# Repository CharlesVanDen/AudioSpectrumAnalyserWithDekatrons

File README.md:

# AudioSpectrumAnalyserWithDekatrons

I started this project with twenty 6802 dekatrons, not really knowing what the end result would be. That's why it was called TwentyDekatrons. 
Then I discovered the MSGEQ7 and it turned into an Stereo Audio Spectrum Analyzer with only seven Dekatrons. And now it's an article 
in Elektor issue september/ocotober 2022! For the extensive documentation, see: https://www.elektormagazine.nl/labs/i-finally-found-a-useful-application-for-dekatrons and https://www.elektor.com

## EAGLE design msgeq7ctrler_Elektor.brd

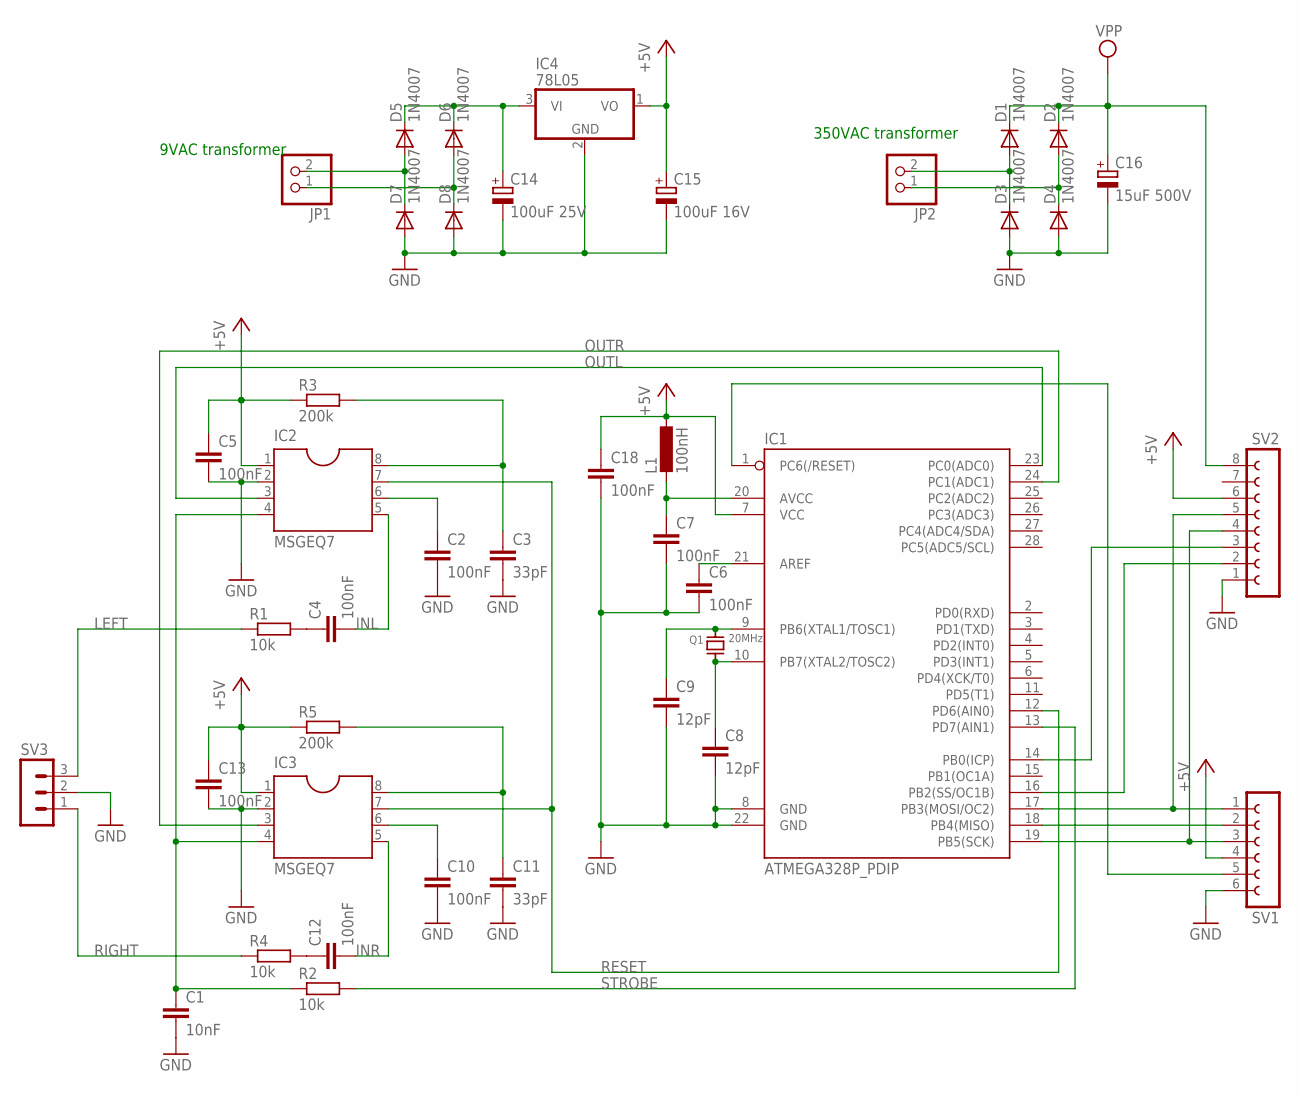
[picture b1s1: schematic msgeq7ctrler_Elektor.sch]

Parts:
C1: 10nF; C025-025X050
C2, C4, C5, C6, C7, C10, C12, C13, C18: 100nF; C025-025X050
C3, C11: 33pF; C025-025X050
C8, C9: 12pF; C025-025X050
C14: 100uF 25V; E2,5-6E
C15: 100uF 16V; E2,5-6E
C16: 15uF 500V; EB20D
D1, D2, D3, D4, D5, D6, D7, D8: 1N4007; DO41-10
IC1: ATMEGA328P_PDIP; DIL28-3
IC2, IC3: MSGEQ7; DIL08
IC4: 78L05; TO92SIL
JP1, JP2: PINHD-1X2; 1X02
L1: 100nH; 0207/10
Q1: 20MHz; XTAL
R1, R2, R4: 10k; 0207/12
R3, R5: 200k; 0207/12
SV1: FE06-1; FE06
SV2: FE08-1; FE08
SV3: MA03-1

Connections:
+5V: C5.1, C13.1, C15.+, C18.1, IC1.7 (VCC), IC2.1, IC3.1, IC4.1 (VO), L1.1, R3.1, R5.1, SV1.4, SV2.6
GND: C1.2, C2.2, C3.2, C5.2, C6.2, C7.2, C8.2, C9.2, C10.2, C11.2, C13.2, C14.-, C15.-, C16.-, C18.2, D3.A, D4.A, D7.A, D8.A, IC1.8 (GND), IC1.22 (GND), IC2.2, IC3.2, IC4.2 (GND), SV1.6, SV2.1, SV3.2
INL: C4.2, IC2.5
INR: C12.2, IC3.5
LEFT: R1.1, SV3.3
unnamed: C3.1, IC2.8, R3.2
unnamed: C4.1, R1.2
unnamed: C9.1, IC1.9 (PB6(XTAL1/TOSC1)), Q1.P$2
unnamed: C8.1, IC1.10 (PB7(XTAL2/TOSC2)), Q1.P$1
unnamed: C7.1, IC1.20 (AVCC), L1.2
unnamed: C6.1, IC1.21 (AREF)
unnamed: IC1.19 (PB5(SCK)), SV1.3, SV2.4
unnamed: IC1.18 (PB4(MISO)), SV1.2
unnamed: IC1.17 (PB3(MOSI/OC2)), SV1.1, SV2.5
unnamed: IC1.1 (PC6(/RESET)), SV1.5
unnamed: IC1.16 (PB2(SS/OC1B)), SV2.2
unnamed: IC1.14 (PB0(ICP)), SV2.3
unnamed: C11.1, IC3.8, R5.2
unnamed: C12.1, R4.2
unnamed: D1.A, D3.C, JP2.2
unnamed: D2.A, D4.C, JP2.1
unnamed: D5.A, D7.C, JP1.2
unnamed: D6.A, D8.C, JP1.1
OUTL: IC1.23 (PC0(ADC0)), IC2.3
OUTR: IC1.24 (PC1(ADC1)), IC3.3
RESET: IC1.12 (PD6(AIN0)), IC2.7, IC3.7
RIGHT: R4.1, SV3.1
STROBE: IC1.13 (PD7(AIN1)), R2.2
STROBE_RC: C1.1, IC2.4, IC3.4, R2.1
VGND: C2.1, IC2.6
VGND1: C10.1, IC3.6
VPP: C16.+, D1.C, D2.C, SV2.8
VPP1: C14.+, D5.C, D6.C, IC4.3 (VI)

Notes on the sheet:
350VAC transformer
9VAC transformer

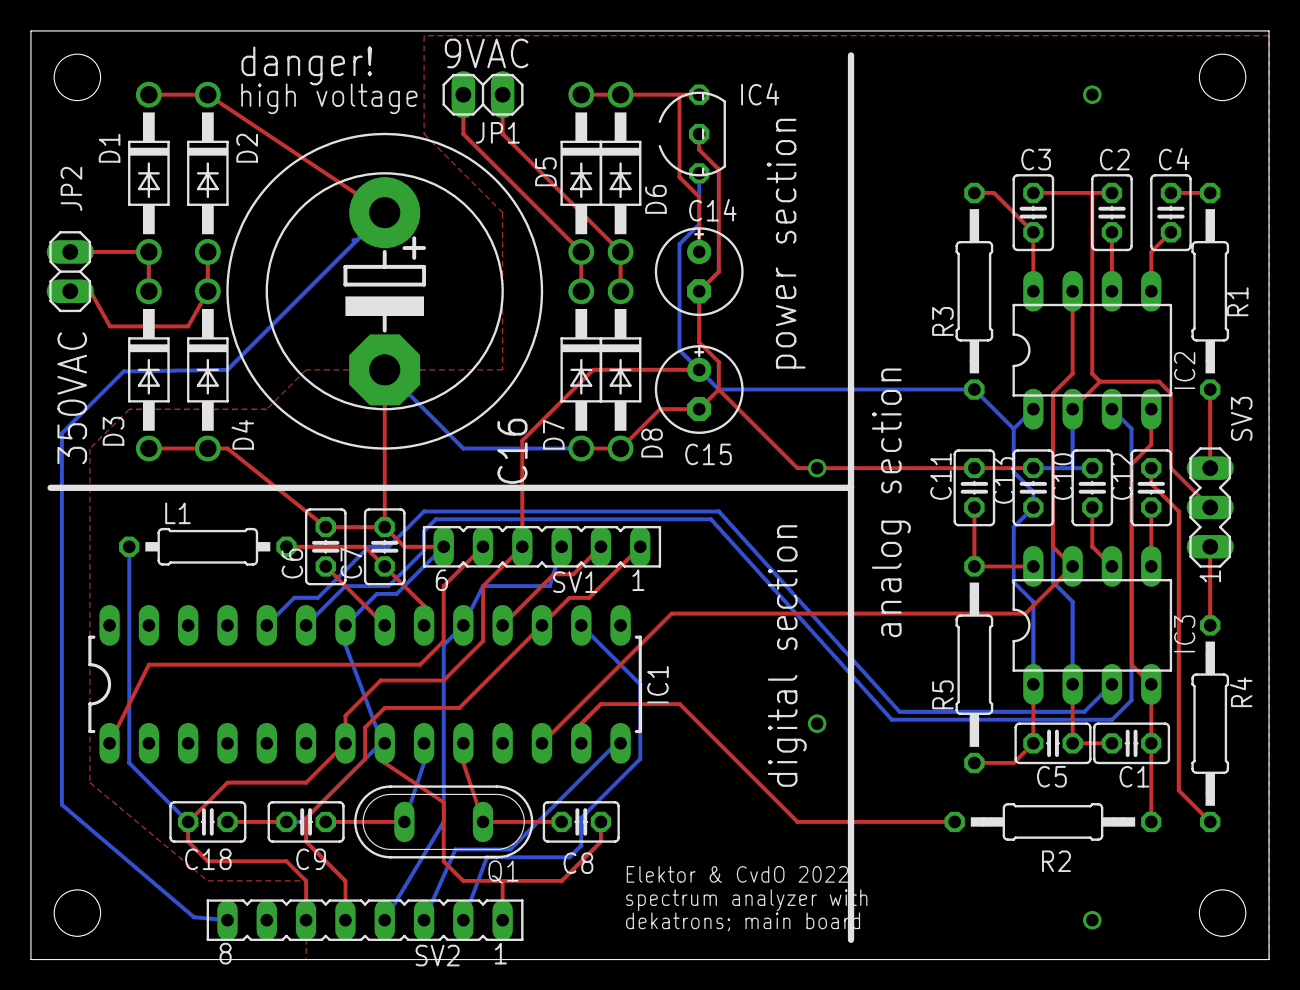
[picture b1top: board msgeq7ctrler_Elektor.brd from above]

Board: 2 copper layers, 80.0 x 60.0 mm, 41 parts (0 on the bottom side), 33 nets.

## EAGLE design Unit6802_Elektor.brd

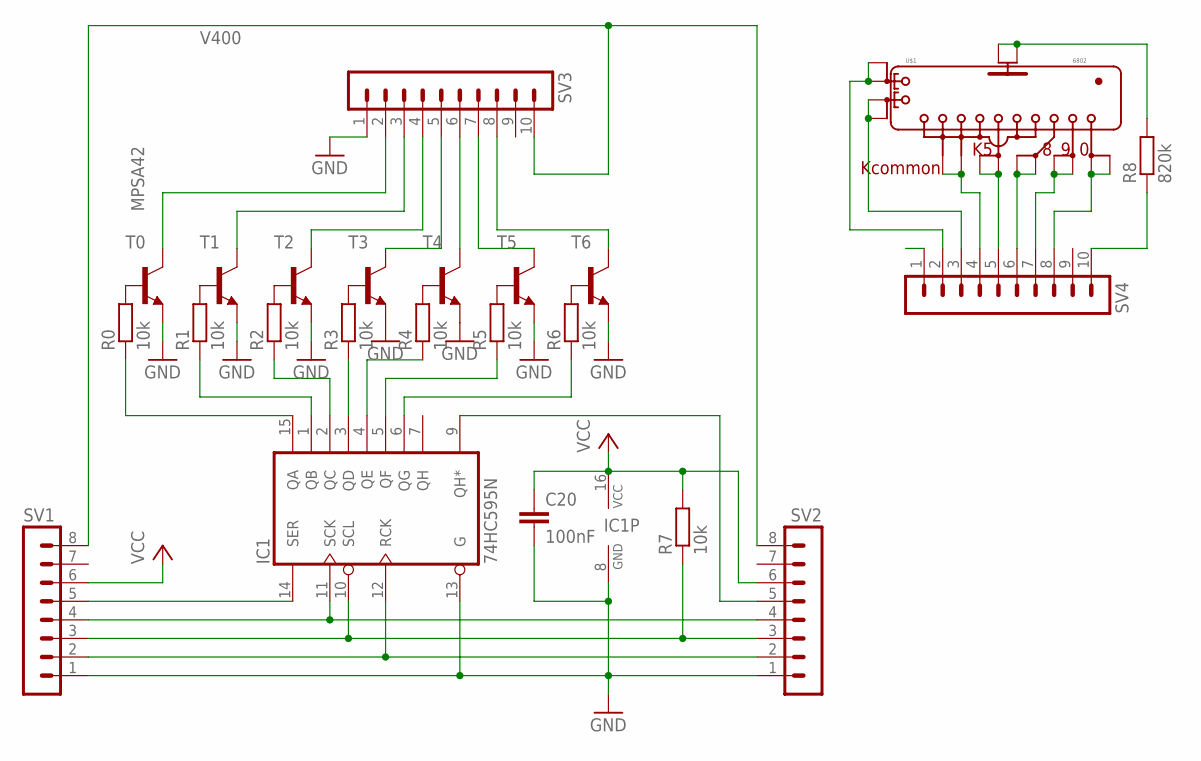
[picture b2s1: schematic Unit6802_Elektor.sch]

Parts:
C20: 100nF; C050-024X044
IC1: 74HC595N; DIL16
R0, R1, R2, R3, R4, R5, R6, R7: 10k; 0207/12
R8: 820k; 0207/12
SV1, SV2: MA08-1
SV3, SV4: MA10-1
T0: MPSA42; TO92-EBC
T1, T2, T3, T4, T5, T6: MPSA42-NPN-TO92-EBC; TO92-EBC
U$1: 6802; OCTAL2

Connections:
GND: C20.2, IC1.8 (GND), IC1.13 (G), SV1.1, SV2.1, SV3.1, T0.E, T1.E, T2.E, T3.E, T4.E, T5.E, T6.E
GND1: SV4.1
unnamed: SV3.4, T2.C
unnamed: SV3.5, T3.C
unnamed: SV3.8, T6.C
unnamed: SV3.7, T5.C
unnamed: SV3.6, T4.C
unnamed: SV3.2, T0.C
unnamed: SV3.3, T1.C
unnamed: SV4.4, U$1.1B (KCOMB), U$1.1C (KCOMA)
unnamed: IC1.15 (QA), R0.1
unnamed: IC1.1 (QB), R1.1
unnamed: IC1.2 (QC), R2.1
unnamed: IC1.3 (QD), R3.1
unnamed: IC1.4 (QE), R4.1
unnamed: IC1.5 (QF), R5.1
unnamed: IC1.6 (QG), R6.1
unnamed: R1.2, T1.B
unnamed: R2.2, T2.B
unnamed: R3.2, T3.B
unnamed: R4.2, T4.B
unnamed: R5.2, T5.B
unnamed: R6.2, T6.B
unnamed: R0.2, T0.B
unnamed: R8.1, SV4.10
unnamed: IC1.14 (SER), SV1.5
unnamed: IC1.11 (SCK), SV1.4, SV2.4
unnamed: IC1.9 (QH*), SV2.5
unnamed: IC1.10 (SCL), R7.1, SV1.3, SV2.3
unnamed: IC1.12 (RCK), SV1.2, SV2.2
unnamed: SV4.5, U$1.2B (K5B), U$1.2C (K5A)
unnamed: SV4.6, U$1.8B (K8B), U$1.8C (K8A)
unnamed: SV4.7, U$1.6B (K9B), U$1.6C (K9A)
unnamed: SV4.8, U$1.7B (K0B), U$1.7C (K0A)
unnamed: SV4.3, U$1.5B (G2B), U$1.5C (G2A)
unnamed: SV4.2, U$1.3B (G1B), U$1.3C (G1A)
unnamed: R8.2, U$1.4B (ANODEB), U$1.4C (ANODEA)
V400: SV1.8, SV2.8, SV3.10
VCC: C20.1, IC1.16 (VCC), R7.2, SV1.6, SV2.6

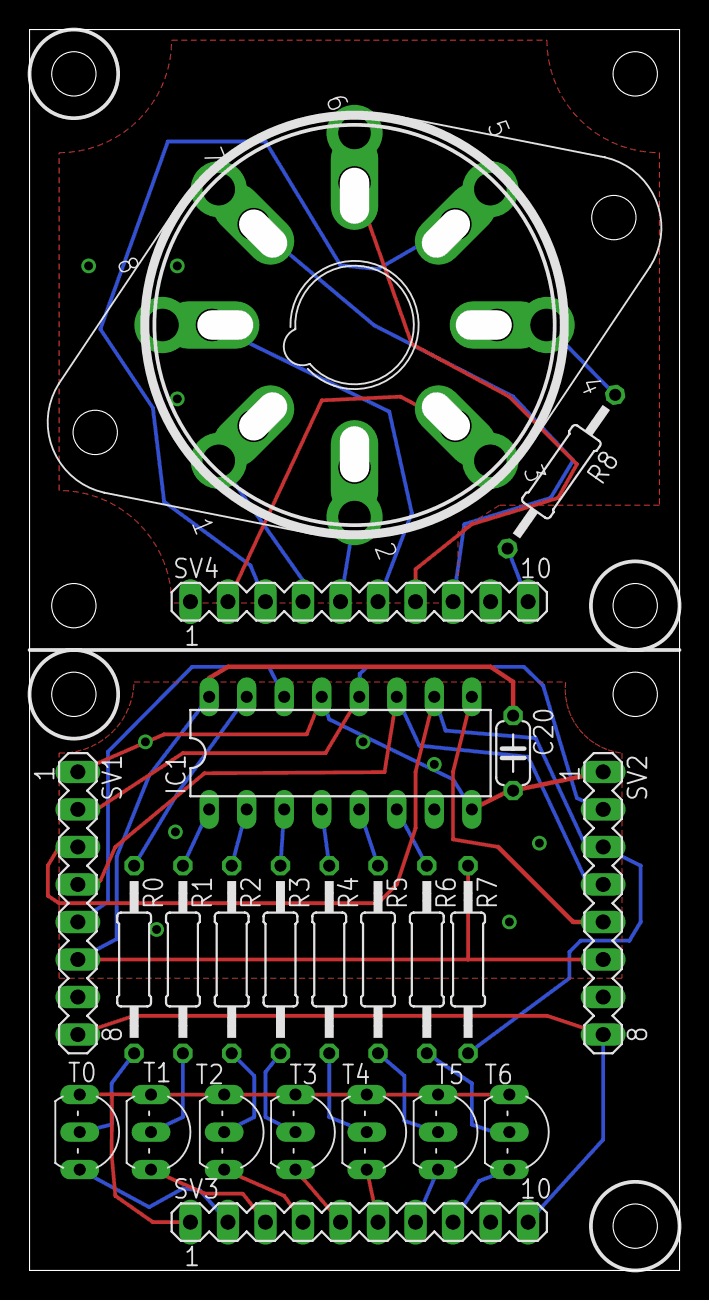
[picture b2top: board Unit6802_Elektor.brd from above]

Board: 2 copper layers, 44.0 x 84.0 mm, 23 parts (0 on the bottom side), 38 nets.

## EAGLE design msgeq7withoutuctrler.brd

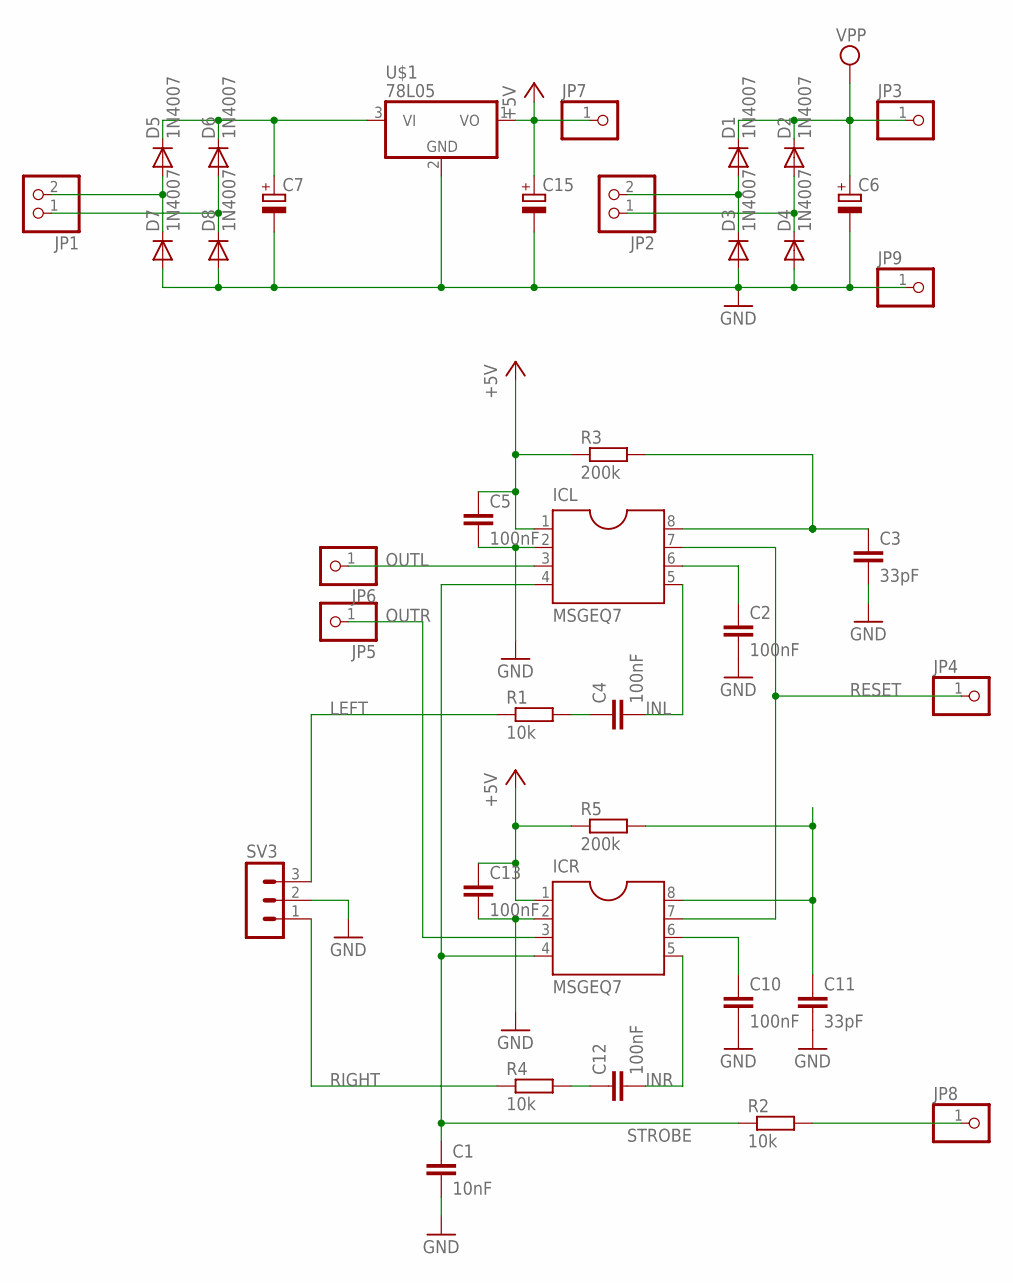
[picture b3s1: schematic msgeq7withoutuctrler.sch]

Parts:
C1: 10nF; C025-025X050
C2, C4, C5, C12, C13: 100nF; C025-025X050
C3, C11: 33pF; C025-025X050
C6: CPOL-EUE5-13; E5-13
C7, C15: CPOL-EUE2,5-6E; E2,5-6E
C10: 100nF; C050-024X044
D1, D2, D3, D4, D5, D6, D7, D8: 1N4007; DO41-10
ICL: MSGEQ7; DIL08
ICR: MSGEQ7; DIL08
JP1, JP2: PINHD-1X2; 1X02
JP3, JP4, JP5, JP6, JP7, JP8, JP9: PINHD-1X1CB; 1X01-CLEANBIG
R1, R2, R4: 10k; 0207/12
R3, R5: 200k; 0207/12
SV3: MA03-1
U$1: 78L05; TO92SIL

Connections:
+5V: C5.1, C13.1, C15.+, ICL.1, ICR.1, JP7.1, R3.1, R5.1, U$1.1 (VO)
GND: C1.2, C2.2, C3.2, C5.2, C6.-, C7.-, C10.2, C11.2, C13.2, C15.-, D3.A, D4.A, D7.A, D8.A, ICL.2, ICR.2, JP9.1, SV3.2, U$1.2 (GND)
INL: C4.2, ICL.5
INR: C12.2, ICR.5
LEFT: R1.1, SV3.3
unnamed: JP8.1, R2.2
unnamed: C3.1, ICL.8, R3.2
unnamed: C4.1, R1.2
unnamed: D5.A, D7.C, JP1.2
unnamed: D6.A, D8.C, JP1.1
unnamed: C11.1, ICR.8, R5.2
unnamed: C12.1, R4.2
unnamed: D1.A, D3.C, JP2.2
unnamed: D2.A, D4.C, JP2.1
OUTL: ICL.3, JP6.1
OUTR: ICR.3, JP5.1
RESET: ICL.7, ICR.7, JP4.1
RIGHT: R4.1, SV3.1
STROBE: C1.1, ICL.4, ICR.4, R2.1
VGND: C2.1, ICL.6
VGND1: C10.1, ICR.6
VPP: C6.+, D1.C, D2.C, JP3.1
VPP1: C7.+, D5.C, D6.C, U$1.3 (VI)

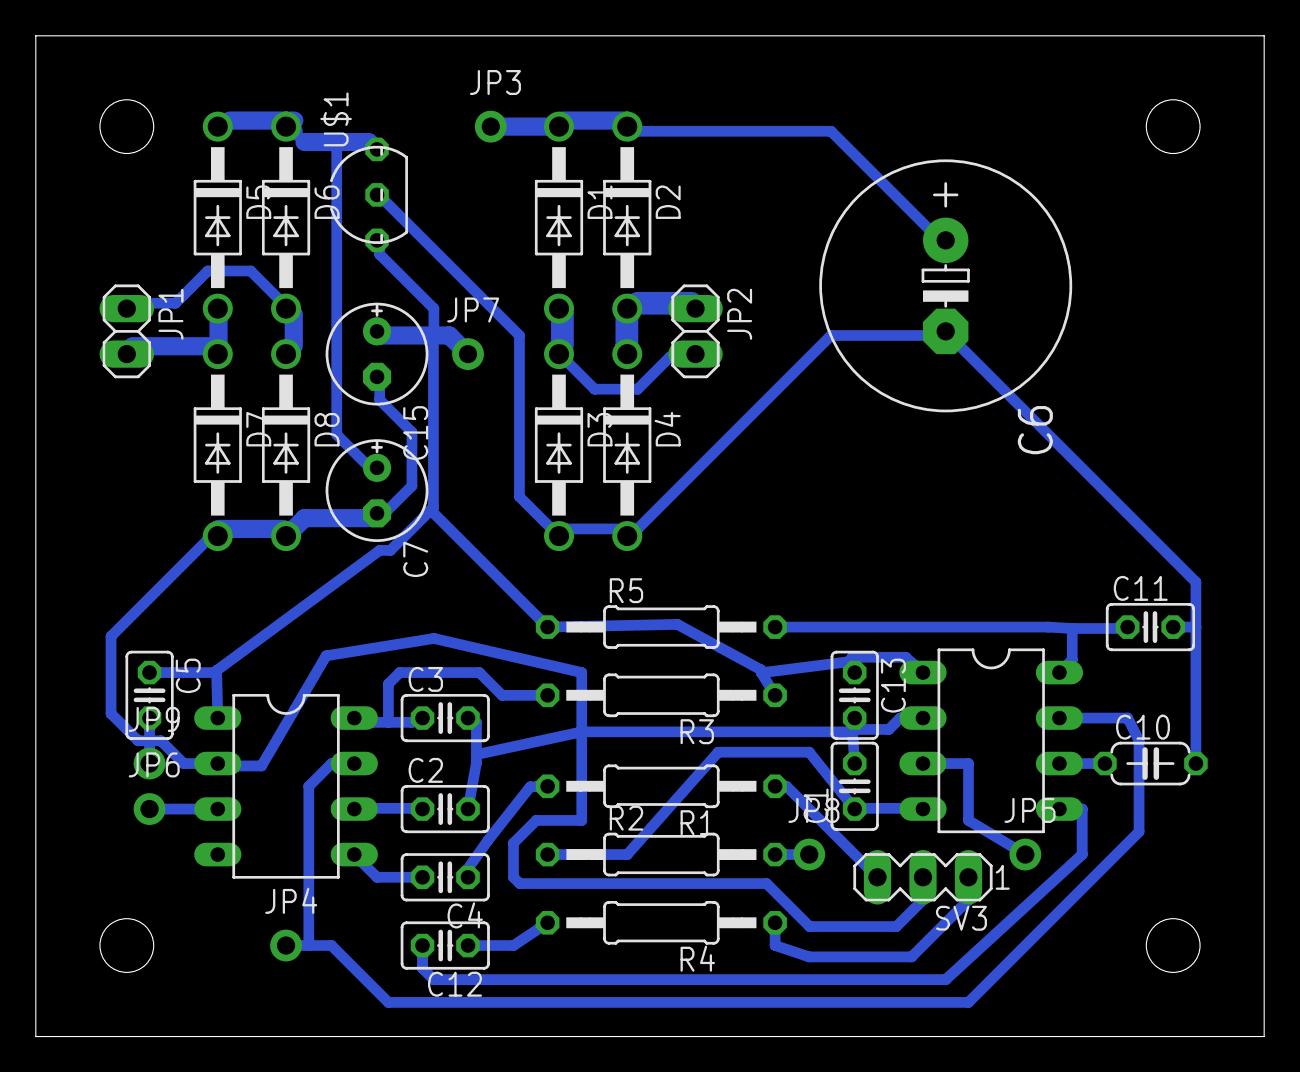
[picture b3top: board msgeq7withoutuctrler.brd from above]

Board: 2 copper layers, 68.6 x 55.9 mm, 38 parts (0 on the bottom side), 23 nets.

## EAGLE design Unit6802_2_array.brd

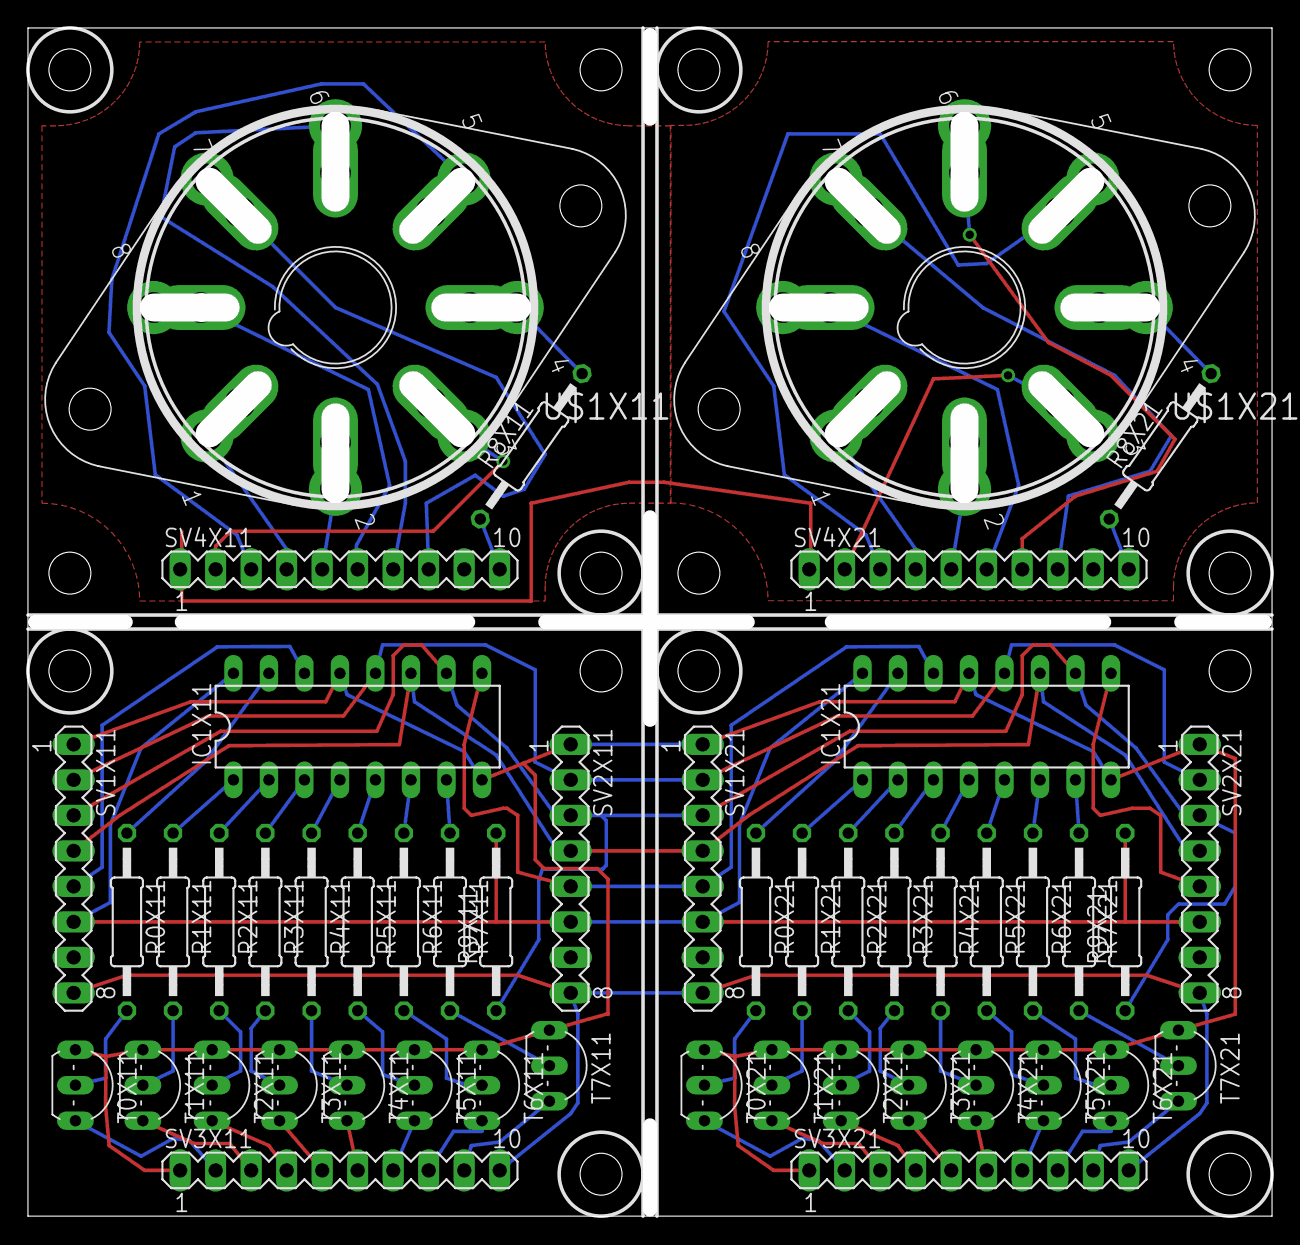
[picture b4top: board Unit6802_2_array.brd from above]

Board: 2 copper layers, 89.0 x 85.0 mm, 48 parts (0 on the bottom side), 75 nets.

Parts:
IC1X11, IC1X21: 74HC595N; DIL16
R0X11, R0X21, R1X11, R1X21, R2X11, R2X21, R3X11, R3X21, R4X11, R4X21, R5X11, R5X21, R6X11, R6X21, R7X11, R7X21, R9X11, R9X21: 10k; 0207/12
R8X11, R8X21: 820k; 0207/12
SV1X11, SV1X21, SV2X11, SV2X21: MA08-1
SV3X11, SV3X21, SV4X11, SV4X21: MA10-1
T0X11, T0X21: MPSA42; TO92-EBC
T1X11, T1X21, T2X11, T2X21, T3X11, T3X21, T4X11, T4X21, T5X11, T5X21, T6X11, T6X21, T7X11, T7X21: TO92-EBC
U$1X11, U$1X21: 6802; OCTAL2

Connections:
GND: IC1X11.8, IC1X11.13, IC1X21.8, IC1X21.13, SV1X11.1, SV1X21.1, SV2X11.1, SV2X21.1, SV3X11.1, SV3X21.1, T0X11.E, T0X21.E, T1X11.E, T1X21.E, T2X11.E, T2X21.E, T3X11.E, T3X21.E, T4X11.E, T4X21.E, T5X11.E, T5X21.E, T6X11.E, T6X21.E, T7X11.E, T7X21.E
unnamed: SV3X11.4, T2X11.C
unnamed: SV3X21.4, T2X21.C
unnamed: SV3X11.5, T3X11.C
unnamed: SV3X21.5, T3X21.C
unnamed: SV3X11.8, T6X11.C
unnamed: SV3X21.8, T6X21.C
unnamed: SV3X11.7, T5X11.C
unnamed: SV3X21.7, T5X21.C
unnamed: SV3X11.6, T4X11.C
unnamed: SV3X21.6, T4X21.C
unnamed: SV3X11.2, T0X11.C
unnamed: SV3X21.2, T0X21.C
unnamed: SV3X11.3, T1X11.C
unnamed: SV3X21.3, T1X21.C
unnamed: SV4X11.4, U$1X11.1B, U$1X11.1C
unnamed: SV4X21.4, U$1X21.1B, U$1X21.1C
unnamed: IC1X11.15, R0X11.1
unnamed: IC1X21.15, R0X21.1
unnamed: IC1X11.1, R1X11.1
unnamed: IC1X21.1, R1X21.1
unnamed: IC1X11.2, R2X11.1
unnamed: IC1X21.2, R2X21.1
unnamed: IC1X11.3, R3X11.1
unnamed: IC1X21.3, R3X21.1
unnamed: IC1X11.4, R4X11.1
unnamed: IC1X21.4, R4X21.1
unnamed: IC1X11.5, R5X11.1
unnamed: IC1X21.5, R5X21.1
unnamed: IC1X11.6, R6X11.1
unnamed: IC1X21.6, R6X21.1
unnamed: R1X11.2, T1X11.B
unnamed: R1X21.2, T1X21.B
unnamed: R2X11.2, T2X11.B
unnamed: R2X21.2, T2X21.B
unnamed: R3X11.2, T3X11.B
unnamed: R3X21.2, T3X21.B
unnamed: R4X11.2, T4X11.B
unnamed: R4X21.2, T4X21.B
unnamed: R5X11.2, T5X11.B
unnamed: R5X21.2, T5X21.B
unnamed: R6X11.2, T6X11.B
unnamed: R6X21.2, T6X21.B
unnamed: R0X11.2, T0X11.B
unnamed: R0X21.2, T0X21.B
unnamed: R7X11.2, T7X11.B
unnamed: R7X21.2, T7X21.B
unnamed: IC1X11.7, R7X11.1
unnamed: IC1X21.7, R7X21.1
unnamed: R8X11.1, SV4X11.10
unnamed: R8X21.1, SV4X21.10
unnamed: IC1X11.14, SV1X11.5
unnamed: IC1X11.11, IC1X21.11, SV1X11.4, SV1X21.4, SV2X11.4, SV2X21.4
unnamed: IC1X11.9, IC1X21.14, SV1X21.5, SV2X11.5
unnamed: IC1X21.9, SV2X21.5
unnamed: IC1X11.10, IC1X21.10, R9X11.1, R9X21.1, SV1X11.3, SV1X21.3, SV2X11.3, SV2X21.3
unnamed: IC1X11.12, IC1X21.12, SV1X11.2, SV1X21.2, SV2X11.2, SV2X21.2
unnamed: SV4X11.5, U$1X11.2B, U$1X11.2C
unnamed: SV4X21.5, U$1X21.2B, U$1X21.2C
unnamed: SV4X11.6, U$1X11.8B, U$1X11.8C
unnamed: SV4X21.6, U$1X21.8B, U$1X21.8C
unnamed: SV4X11.7, U$1X11.6B, U$1X11.6C
unnamed: SV4X21.7, U$1X21.6B, U$1X21.6C
unnamed: SV4X11.8, U$1X11.7B, U$1X11.7C
unnamed: SV4X21.8, U$1X21.7B, U$1X21.7C
unnamed: SV4X11.3, U$1X11.5B, U$1X11.5C
unnamed: SV4X21.3, U$1X21.5B, U$1X21.5C
unnamed: SV4X11.2, U$1X11.3B, U$1X11.3C
unnamed: SV4X21.2, U$1X21.3B, U$1X21.3C
unnamed: R8X11.2, U$1X11.4B, U$1X11.4C
unnamed: R8X21.2, U$1X21.4B, U$1X21.4C
unnamed: SV3X11.9, T7X11.C
unnamed: SV3X21.9, T7X21.C
V400X11: SV1X11.8, SV1X21.8, SV2X11.8, SV2X21.8, SV3X11.10, SV3X21.10
VCCX11: IC1X11.16, IC1X21.16, R9X11.2, R9X21.2, SV1X11.6, SV1X21.6, SV2X11.6, SV2X21.6

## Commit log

2022-04-12 Atmel Studio files for the atmega328
2022-04-12 CADsoft Eagle pcb design files
2022-04-12 Gerber files
2022-04-13 More Eagle files
2022-04-13 The hex file for the ATMEGA328P
2022-04-20 Delete Unit6802.sch
    Delete pcb file; will upload better version later
2022-04-20 Delete Unit6802_2.brd
    Delete pcb file; will upload better version later
2022-04-20 Delete Unit6802_2_array18.zip
    Delete pcb file; will upload better version later
2022-04-20 Delete Unit6802_2.sch
    Delete pcb file; will upload better version later
2022-04-20 Delete Unit6802_2_array.brd
    Delete pcb file; will upload better version later
2022-04-20 Delete msgeq7ctrler.sch
    Delete pcb file; will upload better version later
2022-04-20 Delete msgeq7withoutuctrler.brd
    Delete pcb file; will upload better version later
2022-04-20 Delete msgeq7withoutuctrler.sch
    Delete pcb file; will upload better version later
2022-04-20 PCB files for the unit containing one dekatron (Eagle and Gerber)
2022-04-20 Eagle schematic for the main board
    The main board contains
    * the microcontroller ATMEGA328P
    * two MSGEQ7 aufdio signal analyzer chips (one for left channel, one for right channel)
    * the 5V power supply
    * the 400V power supply
2022-05-13 PCB files for the main board (Eagle and Gerber)

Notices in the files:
parts and their libraries:
SparkFun-DigitalIC: Licensing: Creative Commons ShareAlike 4.0 International - https://creativecommons.org/licenses/by-sa/4.0
